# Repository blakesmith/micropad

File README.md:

# Micropad

This is a small macropad keyboard I built, mostly for controlling my music while working.

It includes:

- KiCAD schematic and PCB design.
- OpenSCAD case and top plate designs.
- Custom Rust firmware for the STM32F042 microcontroller
- Bill of materials, of all the components used.

License: MIT

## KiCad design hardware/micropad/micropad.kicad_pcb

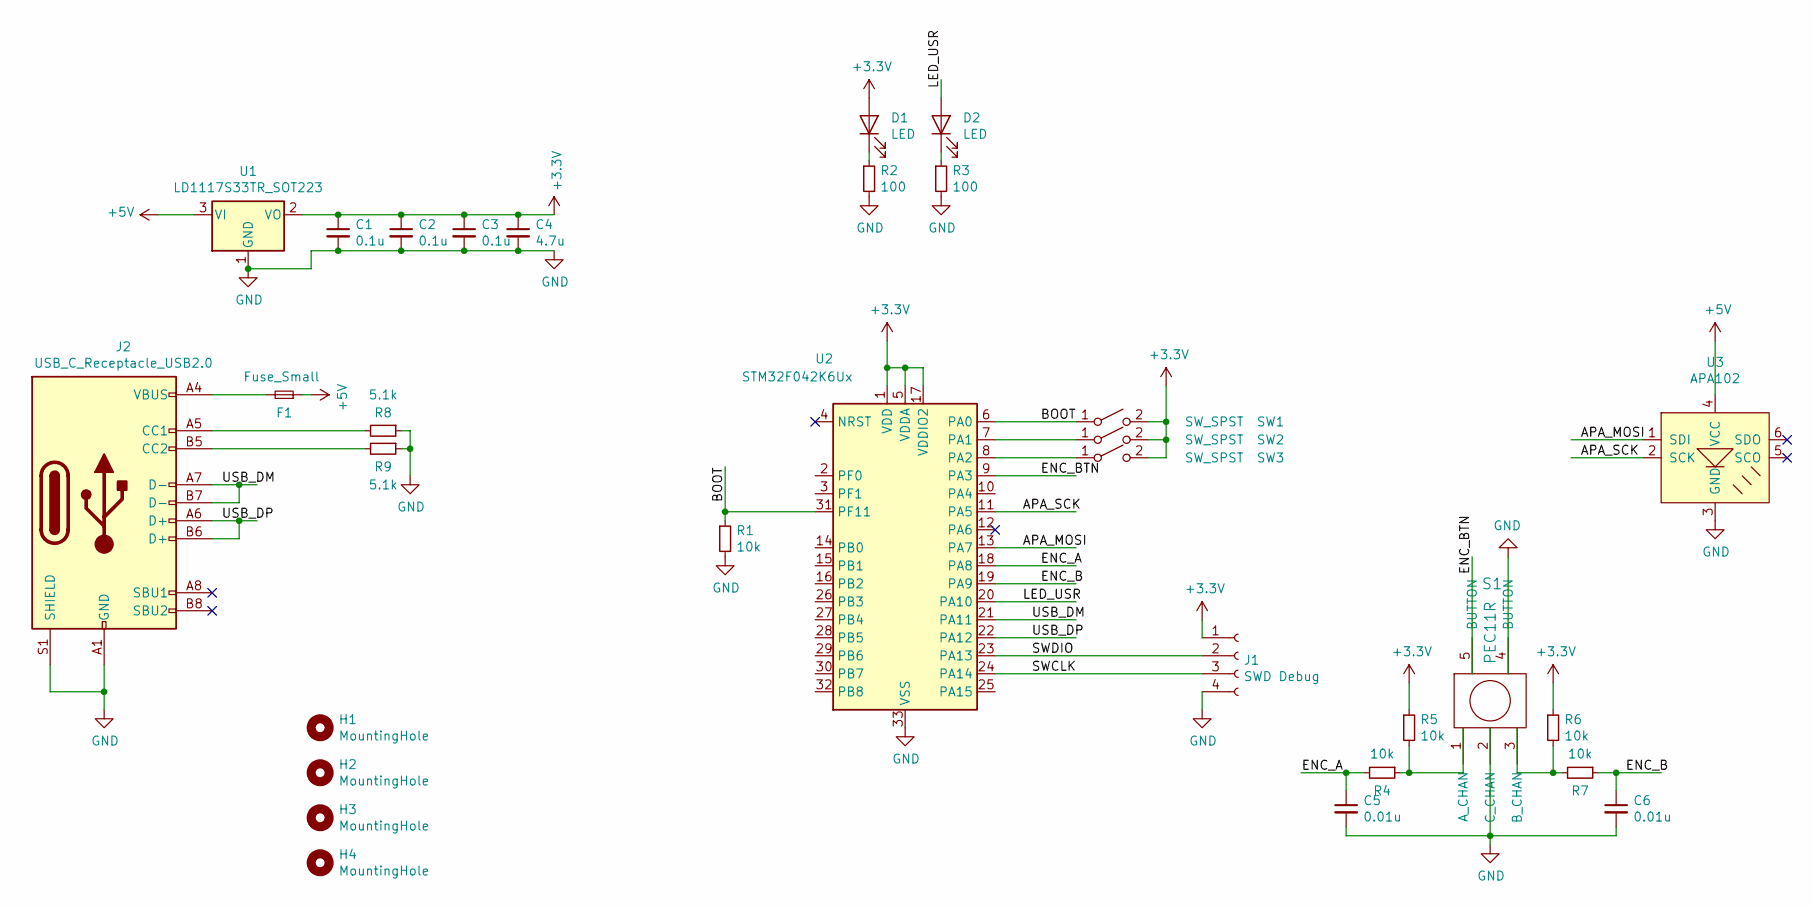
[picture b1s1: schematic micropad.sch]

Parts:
C1, C2, C3: 0.1u; C_0805
C4: 4.7u; C_0805
C5, C6: 0.01u; C_0805
D1, D2: LED; LED_0805
F1: Fuse_Small; C_0603
H1, H2, H3, H4: MountingHole; MountingHole_3.2mm_M3_ISO7380_Pad
J1: SWD Debug; REDFIT_IDC_SKEDD_CONN_4PIN
J2: USB_C_Receptacle_USB2.0; USB_C_Receptacle_Molex_1054500101
R1, R4, R5, R6, R7: 10k; R_0805
R2, R3: 100; R_0805
R8, R9: 5.1k; R_0805
S1: PEC11R; PEC11
SW1: SW_SPST; SW_Cherry_MX1A_2.00u_Plate
SW2, SW3: SW_SPST; SW_Cherry_MX1A_1.00u_Plate
U1: LD1117S33TR_SOT223; SOT-223
U2: STM32F042K6Ux; QFN-32-1EP_5x5mm_Pitch0.5mm
U3: APA102; LED_RGB_5050-6

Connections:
+3V3: C1.1, C2.1, C3.1, C4.1, D1.2 (A), J1.1, R5.1, R6.1, SW1.2 (B), SW2.2 (B), SW3.2 (B), U1.2 (VO), U2.1 (VDD), U2.5 (VDDA), U2.17 (VDDIO2)
+5V: F1.1, U1.3 (VI), U3.4 (VCC)
/APA_MOSI: U2.13 (PA7), U3.1 (SDI)
/APA_SCK: U2.11 (PA5), U3.2 (SCK)
/BOOT: R1.1, SW1.1 (A), U2.6 (PA0), U2.31 (PF11)
/ENC_A: C5.1, R4.2, U2.18 (PA8)
/ENC_B: C6.1, R7.1, U2.19 (PA9)
/ENC_BTN: S1.5 (BUTTON), U2.9 (PA3)
/LED_USR: D2.2 (A), U2.20 (PA10)
/SWCLK: J1.3, U2.24 (PA14)
/SWDIO: J1.2, U2.23 (PA13)
/USB_DM: J2.A7 (D-), J2.B7 (D-), U2.21 (PA11)
/USB_DP: J2.A6 (D+), J2.B6 (D+), U2.22 (PA12)
GND: C1.2, C2.2, C3.2, C4.2, C5.2, C6.2, J1.4, J2.A1 (GND), J2.A12 (GND), J2.B1 (GND), J2.B12 (GND), J2.S1 (SHIELD), R1.2, R2.2, R3.2, R8.1, R9.1, S1.2 (C_CHAN), S1.4 (BUTTON), U1.1 (GND), U2.33 (VSS), U3.3 (GND)
unnamed: D1.1 (K), R2.1
unnamed: D2.1 (K), R3.1
unnamed: F1.2, J2.A4 (VBUS), J2.A9 (VBUS), J2.B4 (VBUS), J2.B9 (VBUS)
unnamed: J2.A5 (CC1), R8.2
unnamed: J2.B5 (CC2), R9.2
unnamed: R4.1, R5.2, S1.1 (A_CHAN)
unnamed: R6.2, R7.2, S1.3 (B_CHAN)
unnamed: SW2.1 (A), U2.7 (PA1)
unnamed: SW3.1 (A), U2.8 (PA2)

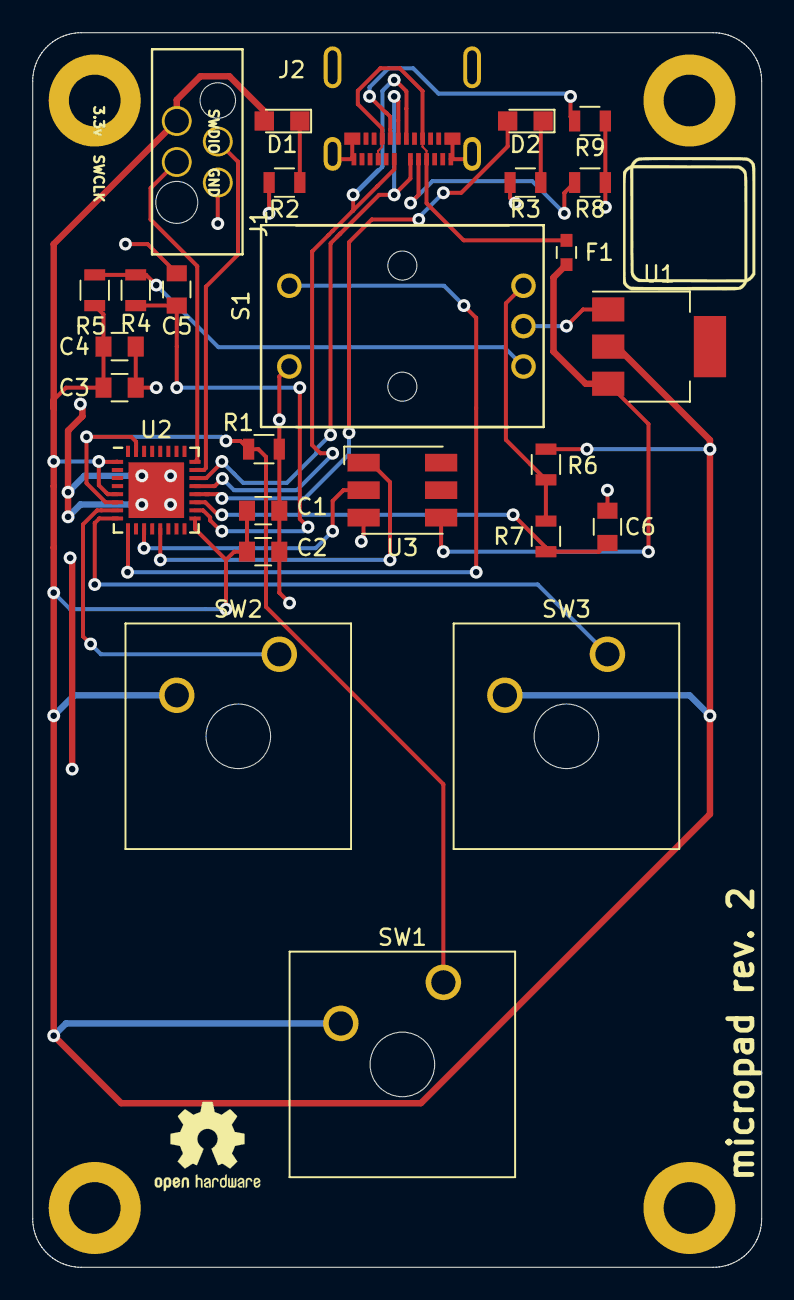
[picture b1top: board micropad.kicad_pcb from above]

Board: 2 copper layers, 45.1 x 76.5 mm, 31 parts (0 on the bottom side), 23 nets.

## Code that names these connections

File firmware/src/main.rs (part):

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use hal::{
    delay::Delay,
    gpio::{
        gpioa::{PA0, PA1, PA10, PA2, PA3, PA5, PA6, PA7, PA8, PA9},
        Alternate, Floating, Input, Output, PullDown, PullUp, PushPull, AF0,
    },
    pac,
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}));

struct Devices {
    ok_led: PA10<Output<PushPull>>,
    delay: Delay,
    play_pause: PA0<Input<PullDown>>,
    next: PA2<Input<PullDown>>,
    prev: PA1<Input<PullDown>>,
    enc_btn: PA3<Input<PullUp>>,
    apa102: Apa102<
        spi::Spi<
            hal::stm32::SPI1,
            PA5<Alternate<AF0>>,
            PA6<Alternate<AF0>>,
            PA7<Alternate<AF0>>,
            spi::EightBit,
        >,
    >,
    encoder: RotaryEncoder<PA8<Input<Floating>>, PA9<Input<Floating>>>,
}

#[derive(Clone)]
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        apa102: &mut Apa102<
            spi::Spi<
                hal::stm32::SPI1,
                PA5<Alternate<AF0>>,
                PA6<Alternate<AF0>>,
                PA7<Alternate<AF0>>,
                spi::EightBit,
            >,
        >,
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            usb_dm,
            usb_dp,
        ) = (
            gpioa.pa0.into_pull_down_input(cs), // Play pause button, has a 10k pull down resistor on the board
            gpioa.pa1.into_pull_down_input(cs), // Next button
            gpioa.pa2.into_pull_down_input(cs), // Prev button
            gpioa.pa3.into_pull_up_input(cs),   // Encoder button
            gpioa.pa8.into_floating_input(cs), // Encoder A, has a 10k pull up resistor on the board
            gpioa.pa9.into_floating_input(cs), // Encoder B, has a 10k pull up resistor on the board
            gpioa.pa10.into_push_pull_output(cs), // LED usr
            gpioa.pa5.into_alternate_af0(cs),  // APA102 SPI SCK
            gpioa.pa6.into_alternate_af0(cs),  // APA102 SPI MISO
            gpioa.pa7.into_alternate_af0(cs),  // APA102 SPI MOSI
            gpioa.pa11,                        // USB dm
            gpioa.pa12,                        // USB dp
        );
        let delay = Delay::new(core.SYST, &rcc);
        let spi = spi::Spi::spi1(
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        let encoder = RotaryEncoder::new(enc_cw, enc_ccw);
        let usb = hal::usb::Peripheral {
            usb: peripherals.USB,
            pin_dm: usb_dm,
            pin_dp: usb_dp,
        };

        unsafe {
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
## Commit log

2020-11-12 Add initial bom
2020-11-12 Add initial schema, update bom
2020-11-12 Continue connecting peripherals to the microcontroller
2020-11-14 Add USB footprint
2020-11-15 Get PCB footprints to load
2020-11-15 Check in netlist
2020-11-15 Check in initial blinky firmware
2020-11-15 Add usb and apa102 dependencies
2020-11-16 Start init the usb device
2020-11-16 Wire in the keyboard to send play/pause
2020-11-16 Expose hid as public
2020-11-16 Assign more pins
2020-11-16 Swap in an APA102 instead of the OLED screen
2020-11-16 Add next and prev button media keys
2020-11-17 Start placing preliminary components
2020-11-17 Use a QFN32 package that's easier to work with
2020-11-17 Add mounting holes
2020-11-19 Route remaining tracks
2020-11-19 Add fuse, fixup DRC and labels
2020-11-19 Remove OLED screen, replace with APA102 LED
2020-11-20 Add initial rotary encoder port
2020-11-20 Integrate encoder into main loop
2020-11-20 Start initial plate in the case
2020-11-23 Start playing with top plate width
2020-11-23 Reduce board width
2020-11-23 Line up mounting holes
2020-11-23 Refill zones
2020-11-23 Line up mounting holes better and round PCB corners
2020-11-23 Update to plated mounting holes
2020-11-23 Minor USB and silk screen adjustments
2020-11-24 Add initial encoder and apa cutouts
2020-11-24 Round more cutout corners
2020-11-24 Add usb cutout
2020-11-24 Adjust mounting hole sizes
2020-11-24 Add TODO list
2020-11-24 Add a possible encoder knob
2020-11-24 Case starting to come together
2020-11-25 Adjust switch placement, based on height
2020-11-25 Get standoffs lined up again
2020-11-25 Add bottom case mounting holes
2020-11-25 Add encoder model
2020-11-25 Add usb case cutout
2020-11-25 Color the case
2020-11-25 Add chamfer to outer case
2020-11-25 Add in some tolerances for the PCB and top plate
2020-11-25 Add some tolerance for the tallest PCB component
2020-11-25 Try a 6mm standoff
2020-11-26 Use temporary connector for SWD programming
2020-11-26 Add logo
2020-11-26 Check in DXF files
2020-11-26 Fixup DRC
2020-11-26 Cleanup LED user track
2020-11-26 Refill PCB
2020-11-27 Order boards and components
2020-11-27 Switch the play_pause button to floating
2020-11-27 Add target that outputs a release binary
2020-12-07 Make an indent for the mounting hole screws
2020-12-07 Make mounting hole indents screw head size accurate
2020-12-10 Get main media buttons working
2020-12-10 Adjust color values
2020-12-10 Start pulsing LED on button push
2020-12-10 Fix blue color phase shifting
2020-12-10 Toggle the LED when the encoder value changes
2020-12-10 Pulse the main indicator LED on volume adjustments
2020-12-10 Volume up is sort of working
2020-12-10 Add in HID delay
2020-12-10 Report size is 8, not 7
2020-12-10 Softer color pulses
2020-12-10 Adjust HID delay
2020-12-10 Smoother volume responsiveness
2020-12-10 Encoder button mutes
2020-12-12 Minor top plate and case tweaks
2020-12-12 Adjust the case width a bit more for tolerances
2020-12-12 Make encoder cutout a little bit bigger
2020-12-15 Add potential USB-C part
2020-12-15 Add openocd flash script
2020-12-15 Add initial usb serial allocation
2020-12-16 Get USB serial and keyboard working on the same device
2020-12-16 Shorten interrupt disable window
2020-12-18 Add start of a serial protocol
2020-12-18 Hold back 1K of flash for program storage
2020-12-18 Add basic protocol
2020-12-18 Add untested enabling / disabling RGB LED
2020-12-19 Move to safe critical section mutexes and refcalls instead of unsafe static muts
2020-12-19 Add initial command line client interface
2020-12-21 Move embedded specific read / write functions out of protocol file
2020-12-21 Break out protocol into its own separate lib
2020-12-21 Rename to ctrl
2020-12-21 Send a ping command to the micropad
2020-12-21 Enabling and disabling the LED is working
2020-12-22 Remove enable / disable LED messages, replace with set LED brightness
2020-12-22 Replace USB micro connector with USB-C connector
2020-12-22 Add additional ground connections to the STM32
2020-12-22 Revision 2
2020-12-23 Change PCB mounting holes to M3
2020-12-23 Adjust case / top plate mounting hole sizes and positions for M3 screws
2020-12-23 Adjust usb connector dimensions for USB-C
2020-12-23 Adjust heights for new set of standoffs
2020-12-23 Move usb cutout to just above the PCB
2020-12-23 Adjust switch cutout locations and tweak encoder cutout location
2020-12-23 Make the PCB non rounded in modeling
2020-12-26 Order rev. 2 of PCB
2020-12-26 Get DFU firmware update working
2020-12-28 No need for dfu prefixes
2020-12-28 Add indirect concept of a mode, for different key setups
2020-12-28 Send both report types, and swap modes on encoder press
2020-12-28 Replace second mode with keyboard nav mode
2020-12-28 Type alias Mode
2020-12-28 Finish out multiple modes
2020-12-28 Change message frame size to 8 bytes
2020-12-29 Rename 'Response' to 'ResponseCode'
2020-12-29 Update serial protocol documentation with additional response values
2020-12-29 Add untested method to get the led brightness
2020-12-29 Untested fetching of mode info
2020-12-29 Sporadic command responses work
2020-12-30 Make sure reads and writes transmit the entire frame before returning
2021-01-03 Add README
2021-01-05 Fix: Correct frame sizing for longer frames
2021-01-08 Rev 2. of case and top plate
2021-05-03 Case, rev 3
2021-05-03 Case, rev 4
2021-05-03 Case, rev 5
2021-05-03 Case, rev 6
2021-05-03 Wrong PCB height
2021-05-04 Case, rev 7
2021-05-04 Expand USB cutout more
